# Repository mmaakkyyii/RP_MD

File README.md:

# RPMD
RP2040 motor driver

# Firmware
https://github.com/mmaakkyyii/RP_MD_firmware

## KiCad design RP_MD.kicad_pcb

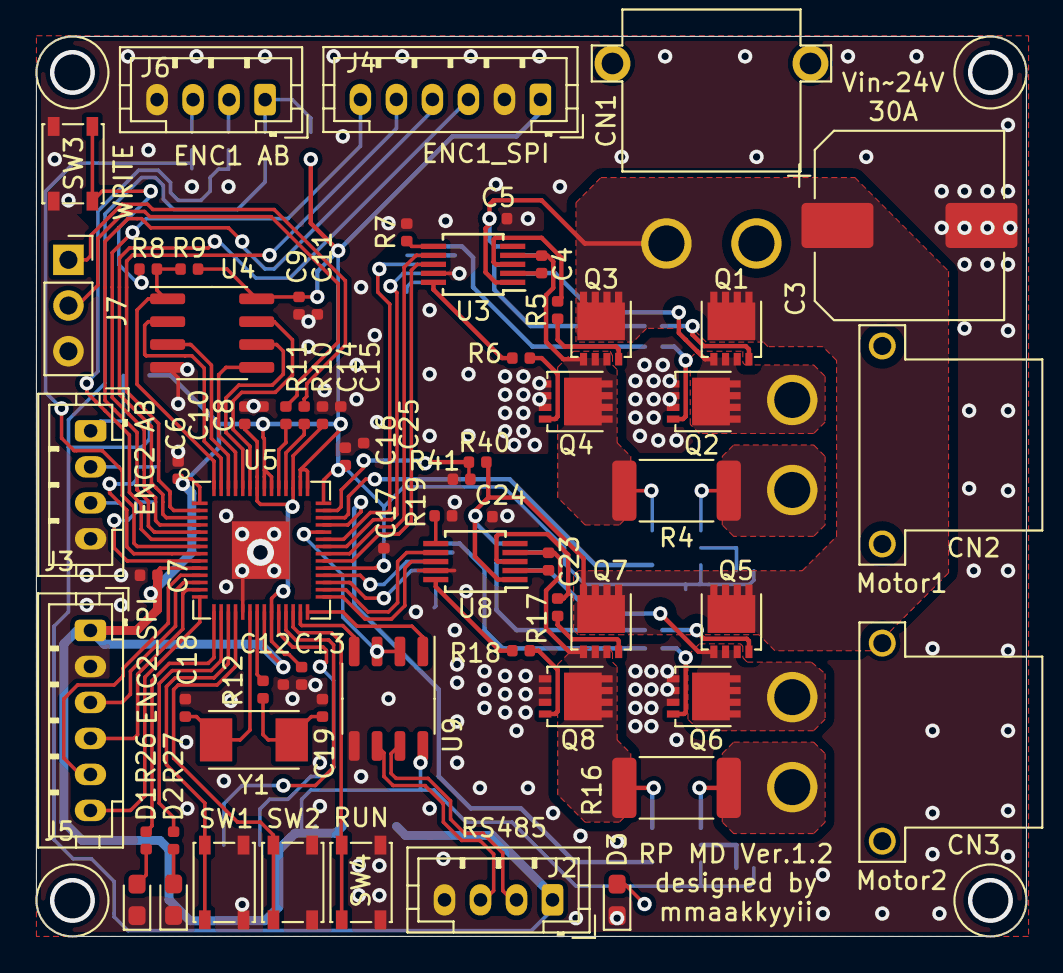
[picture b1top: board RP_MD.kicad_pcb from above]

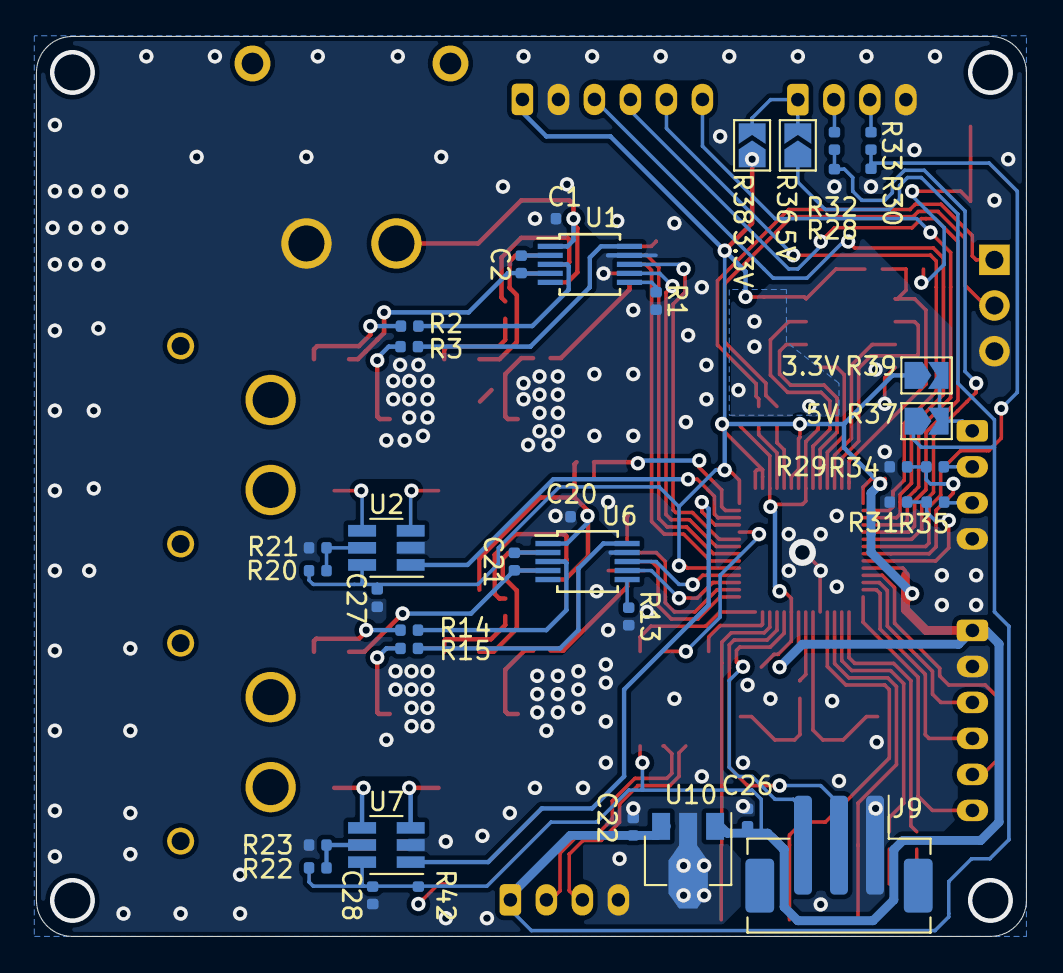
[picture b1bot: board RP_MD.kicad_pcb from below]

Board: 2 copper layers, 55.0 x 50.0 mm, 104 parts (37 on the bottom side), 95 nets.

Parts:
C1, C5, C20, C24, C27, C28: 0.1u 50V; C_0402_1005Metric
C2, C4, C21, C23: 0.22u 50V; C_0402_1005Metric
C3: 220u 50V; CP_Elec_10x10
C6, C7, C8, C9, C10, C12, C13, C16, C17, C25, C26: 0.1u; C_0402_1005Metric
C11, C14, C15: 2u2; C_0402_1005Metric
C18, C19: 27p; C_0402_1005Metric
C22: 0.22u; C_0402_1005Metric
CN1: XT30PW-M
CN2, CN3: XT30PW
D1, D2, D3: LED; LED_0603_1608Metric_Pad1.05x0.95mm_HandSolder
J2, J3, J6: Conn_01x04_Female; JST_PH_B4B-PH-K_1x04_P2.00mm_Vertical
J4, J5: Conn_01x06_Female; JST_PH_B6B-PH-K_1x06_P2.00mm_Vertical
J7: Conn_01x03_Male; PinSocket_1x03_P2.54mm_Vertical
J9: Conn_01x03_Female; JST_PH_B3B-PH-SM4-TB_1x03-1MP_P2.00mm_Vertical
Q1, Q2, Q3, Q4, Q5, Q6, Q7, Q8: TPN1R603PL; TSON_Advance
R1, R7, R9, R13, R19, R20, R21, R22, R23, R28, R29, R30, R31, R32, R33, R34, R35: 10k; R_0402_1005Metric
R2, R3, R5, R6, R14, R15, R17, R18: 10; R_0402_1005Metric
R4, R16: 0.001ohm 2W 1%; R_2512_6332Metric
R8, R12, R26, R27, R42: 1k; R_0402_1005Metric
R10, R11: 27; R_0402_1005Metric
R36, R37, R38, R39: 0; SolderJumper-2_P1.3mm_Open_TrianglePad1.0x1.5mm
R40: 100k; R_0402_1005Metric
R41: 15k; R_0402_1005Metric
SW1, SW2, SW3, SW4: SW_Push; SW_SPST_PTS810
U1, U3, U6, U8: DGD0506A; MSOP-10_3x3mm_P0.5mm
U2, U7: MCP6C02T; SOT-23-6_Handsoldering
U4: W25Q16JV; SOIC-8_3.9x4.9mm_P1.27mm
U5: RP2040
U9: MAX3458ED; SOP-8_3.9x4.9mm_P1.27mm
U10: NJM78L005; SOT-89-3
Y1: 445I23D12M00000; 5_0mmx3_2mm_glass_seal_pak

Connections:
+1V1: C10.1, C13.1, C14.2, U5.23 (DVDD), U5.45 (VREG_VOUT), U5.50 (DVDD)
+3.3V: C6.2, C7.2, C8.1, C9.2, C11.2, C12.1, C15.2, C16.2, C17.2, C26.2, C27.2, C28.2, J4.1, J5.1, R9.2, R20.1, R22.1, R38.1, R39.1, R42.2, U2.6 (Vs), U4.8 (VCC), U5.1 (IOVDD), U5.10 (IOVDD), U5.22 (IOVDD), U5.33 (IOVDD), U5.42 (IOVDD), U5.43 (ADC_AVDD), U5.44 (VREG_VIN), U5.48 (USB_VDD), U5.49 (IOVDD), U7.6 (Vs), U9.8 (VCC), U10.1 (OUT)
+5V: C22.2, J2.1, R36.1, R37.1, U10.3 (IN)
/DE_~RE: U5.38 (GPIO26/ADC0), U9.2 (RE), U9.3 (DE)
/DI: U5.27 (GPIO16), U9.4 (DI)
/ENC1A: R28.1, R32.1, U5.6 (GPIO4)
/ENC1B: R30.1, R33.1, U5.7 (GPIO5)
/ENC2A: R29.1, R34.1, U5.8 (GPIO6)
/ENC2B: R31.1, R35.1, U5.9 (GPIO7)
/MOTOR1_EN1: U1.7 (EN), U5.36 (GPIO24)
/MOTOR1_EN2: U3.7 (EN), U5.35 (GPIO23)
/MOTOR1_PWM1: U1.8 (IN), U5.37 (GPIO25)
/MOTOR1_PWM2: U3.8 (IN), U5.34 (GPIO22)
/MOTOR2_EN1: U5.31 (GPIO20), U6.7 (EN)
/MOTOR2_EN2: U5.30 (GPIO19), U8.7 (EN)
/MOTOR2_PWM1: U5.32 (GPIO21), U6.8 (IN)
/MOTOR2_PWM2: U5.29 (GPIO18), U8.8 (IN)
/RO: U5.28 (GPIO17), U9.1 (RO)
/Sheet625A1F16/LED1: R26.2, U5.15 (GPIO12)
/Sheet625A1F16/LED2: R27.2, U5.16 (GPIO13)
/Sheet625A1F16/QSPI_SCLK: U4.6 (CLK), U5.52 (QSPI_SCLK)
/Sheet625A1F16/QSPI_SD0: U4.5 (DI_IO0), U5.53 (QSPI_SD0)
/Sheet625A1F16/QSPI_SD1: U4.2 (DO/IO1), U5.55 (QSPI_SD1)
/Sheet625A1F16/QSPI_SD2: U4.3 (/WP_IO2), U5.54 (QSPI_SD2)
/Sheet625A1F16/QSPI_SD3: U4.7 (/HOLD_IO3), U5.51 (QSPI_SD3)
/Sheet625A1F16/QSPI_SS_N: R8.1, R9.1, U4.1 (CS), U5.56 (QSPI_SS_N)
/Sheet625A1F16/SPI1_CLK: J4.6, U5.4 (GPIO2)
/Sheet625A1F16/SPI1_CS: J4.3, U5.3 (GPIO1)
/Sheet625A1F16/SPI1_MISO: J4.5, U5.2 (GPIO0)
/Sheet625A1F16/SPI1_MOSI: J4.4, U5.5 (GPIO3)
/Sheet625A1F16/SPI2_CLK: J5.4, U5.13 (GPIO10)
/Sheet625A1F16/SPI2_CS: J5.3, U5.12 (GPIO9)
/Sheet625A1F16/SPI2_MISO: J5.5, U5.11 (GPIO8)
/Sheet625A1F16/SPI2_MOSI: J5.6, U5.14 (GPIO11)
/Sheet625A1F16/SW1: SW1.2, U5.17 (GPIO14)
/Sheet625A1F16/SW2: SW2.2, U5.18 (GPIO15)
/Sheet625A1F16/SWCLK: J9.3, U5.24 (SWCLK)
/Sheet625A1F16/SWDIO: J9.2, U5.25 (SWDIO)
/Sheet625A1F16/USB_DM: J7.1, R11.2
/Sheet625A1F16/USB_DP: J7.2, R10.1
/Sheet625A1F16/VBAT: C25.2, R40.1, R41.2, U5.41 (GPIO29/ADC3)
/Sheet625A1F16/XIN: C18.2, U5.20 (XIN), Y1.1
/Sheet625A1F16/XOUT: R12.2, U5.21 (XOUT)
/Vshunt1: U2.1 (OUT), U5.40 (GPIO28/ADC2)
/Vshunt2: U5.39 (GPIO27/ADC1), U7.1 (OUT)
GND: C1.2, C3.2, C5.2, C6.1, C7.1, C8.2, C9.1, C10.2, C11.1, C12.2, C13.2, C14.1, C15.1, C16.1, C17.1, C18.1, C19.1, C20.2, C22.1, C24.2, C25.1, C26.1, C27.1, C28.1, CN1.2, D1.1 (K), D2.1 (K), D3.1 (K), J2.4, J3.4, J4.2, J5.2, J6.4, J7.3, J9.1, Q2.1 (S), Q4.1 (S), Q6.1 (S), Q8.1 (S), R1.2, R7.2, R13.2, R19.2, R21.2, R23.2, R28.2, R29.2, R30.2, R31.2, R41.1, SW1.1, SW2.1, SW3.1, SW4.2, U1.9 (COM), U2.2 (GND), U3.9 (COM), U4.4 (GND), U5.19 (TESTEN), U5.57 (GND), U6.9 (COM), U7.2 (GND), U8.9 (COM), U9.5 (GND), U10.2 (GND)
unnamed: C2.1, CN2.1, Q1.1 (S), Q2.3 (D), U1.4 (VS)
unnamed: C2.2, U1.2 (VB)
unnamed: C4.1, Q3.1 (S), Q4.3 (D), R4.2, U2.3 (IN+), U3.4 (VS)
unnamed: C4.2, U3.2 (VB)
unnamed: C19.2, R12.1, Y1.2
unnamed: C21.1, CN3.1, Q5.1 (S), Q6.3 (D), U6.4 (VS)
unnamed: C21.2, U6.2 (VB)
unnamed: C23.1, Q7.1 (S), Q8.3 (D), R16.2, U7.3 (IN+), U8.4 (VS)
unnamed: C23.2, U8.2 (VB)
unnamed: CN2.2, R4.1, U2.4 (IN-)
unnamed: CN3.2, R16.1, U7.4 (IN-)
unnamed: D1.2 (A), R26.1
unnamed: D2.2 (A), R27.1
unnamed: D3.2 (A), R42.1
unnamed: J2.2, U9.7 (B)
unnamed: J2.3, U9.6 (A)
unnamed: J3.1, R37.2, R39.2
unnamed: J3.2, R34.2
unnamed: J3.3, R35.2
unnamed: J6.1, R36.2, R38.2
unnamed: J6.2, R32.2
unnamed: J6.3, R33.2
unnamed: R1.1, U1.6 (DT)
unnamed: Q1.2 (G), R2.1
unnamed: R2.2, U1.3 (HO)
unnamed: Q2.2 (G), R3.1
unnamed: R3.2, U1.10 (LO)
unnamed: Q3.2 (G), R5.1
unnamed: R5.2, U3.3 (HO)
unnamed: Q4.2 (G), R6.1
unnamed: R6.2, U3.10 (LO)
unnamed: R7.1, U3.6 (DT)
unnamed: R8.2, SW3.2
unnamed: R10.2, U5.47 (USB_DP)
unnamed: R11.1, U5.46 (USB_DM)
unnamed: R13.1, U6.6 (DT)
unnamed: Q5.2 (G), R14.1
unnamed: R14.2, U6.3 (HO)
unnamed: Q6.2 (G), R15.1
unnamed: R15.2, U6.10 (LO)
unnamed: Q7.2 (G), R17.1
unnamed: R17.2, U8.3 (HO)
unnamed: Q8.2 (G), R18.1
unnamed: R18.2, U8.10 (LO)
unnamed: R19.1, U8.6 (DT)
unnamed: R20.2, R21.1, U2.5 (REF)
unnamed: R22.2, R23.1, U7.5 (REF)
unnamed: SW4.1, U5.26 (RUN)
VCC: C1.1, C3.1, C5.1, C20.1, C24.1, CN1.1, Q1.3 (D), Q3.3 (D), Q5.3 (D), Q7.3 (D), R40.2, U1.1 (VCC), U3.1 (VCC), U6.1 (VCC), U8.1 (VCC)

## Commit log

2022-06-05 add sch_pdf and update BOM
2022-06-05 modify sch_pdf name
2022-06-10 add debug pin and fix AVDD
2022-06-10 update bom
2022-07-16 v1.1
2022-09-04 add sch pdf v1.1
2022-09-04 kicad5
2022-09-04 kicad6 v1.2
2022-10-26 v1.2
2022-11-04 余分なファイル削除
2022-11-04 kicad5のファイル削除
2022-11-04 add readme
2022-11-04 fix readme
2022-11-04 画像変更
